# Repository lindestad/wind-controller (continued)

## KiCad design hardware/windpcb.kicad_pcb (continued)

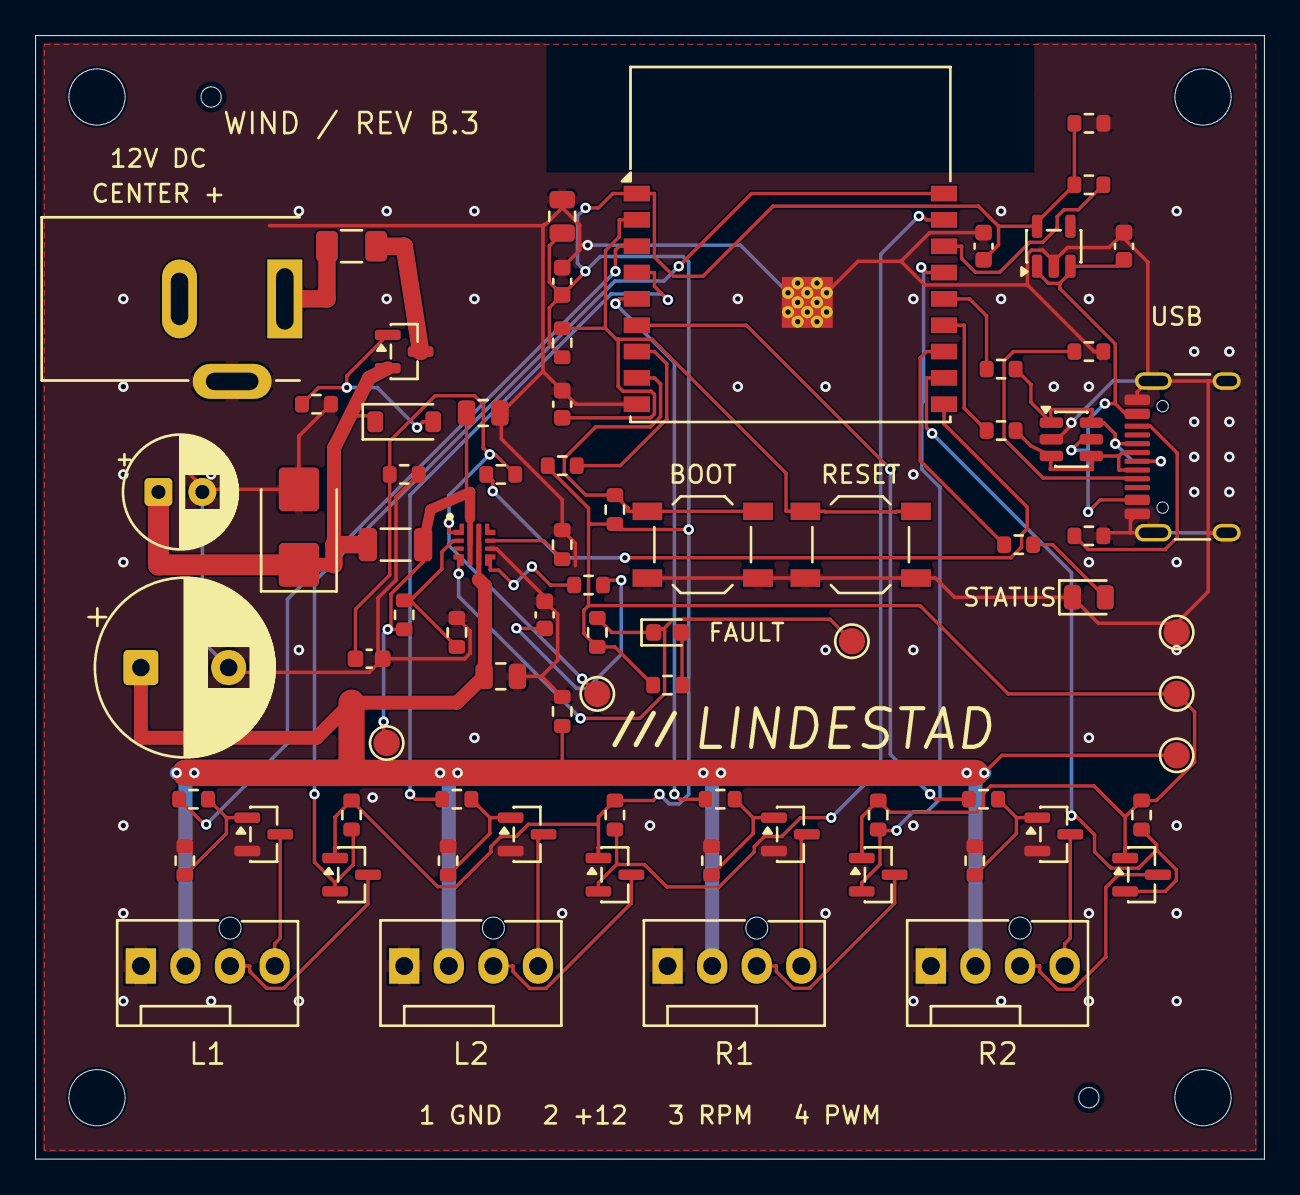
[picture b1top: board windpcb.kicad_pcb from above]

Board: 2 copper layers, 70.0 x 64.0 mm, 82 parts (0 on the bottom side), 49 nets.

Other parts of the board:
H1, H2, H3, H4: M3; MountingHole_3.2mm_M3
H5, H6: JLC TOOL 1.152 NPTH; JLC_Tooling_1.152

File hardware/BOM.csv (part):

Reference,Value,MPN,LCSC,Footprint,Assembly,Notes
U1,ESP32-C3-WROOM-02-N4,ESP32-C3-WROOM-02-N4,C2934560,Wind:RF_Module_ESP32-C3-WROOM-02,SMT,
J2,USB-C DATA,TYPE-C-31-M-12,C165948,Wind:Connector_USB_USB_C_Receptacle_HRO_TYPE-C-31-M-12,SMT,Retained HRO TYPE-C-31-M-12: stocked economical 16-pin USB2 receptacle; shell PTH joints are part of factory assembly.
R1,5.1k,0603WAF5101T5E,C23186,Wind:Resistor_SMD_R_0603_1608Metric,SMT,
R2,5.1k,0603WAF5101T5E,C23186,Wind:Resistor_SMD_R_0603_1608Metric,SMT,
U3,USBLC6-2SC6,USBLC6-2SC6,C7519,Wind:Package_TO_SOT_SMD_SOT-23-6,SMT,
R3,22,0603WAF220JT5E,C23345,Wind:Resistor_SMD_R_0603_1608Metric,SMT,"Basic; 22 ohm 0603 1%, 100 mW. Reject auto-matched ET7222 IC."
R4,22,0603WAF220JT5E,C23345,Wind:Resistor_SMD_R_0603_1608Metric,SMT,"Basic; 22 ohm 0603 1%, 100 mW. Reject auto-matched ET7222 IC."
U2,AP2112K-3.3,AP2112K-3.3TRG1,C51118,Wind:Package_TO_SOT_SMD_SOT-23-5,SMT,
C1,1uF / 50V,CL10A105KB8NNNC,C15849,Wind:Capacitor_SMD_C_0603_1608Metric,SMT,"Basic; 0603 X5R 10%; logic decoupling, -55 to +85 C dielectric range."
C2,1uF / 50V,CL10A105KB8NNNC,C15849,Wind:Capacitor_SMD_C_0603_1608Metric,SMT,"Basic; 0603 X5R 10%; logic decoupling, -55 to +85 C dielectric range."
C3,10uF / 50V,GRM21BR61H106KE43L,C440198,Wind:Capacitor_SMD_C_0805_2012Metric,SMT,Basic; 0805 X5R 10%; 3.3 V reservoir.
C4,100nF / 50V,CC0603KRX7R9BB104,C14663,Wind:Capacitor_SMD_C_0603_1608Metric,SMT,Basic; 0603 X7R 10%.
R5,10k,0603WAF1002T5E,C25804,Wind:Resistor_SMD_R_0603_1608Metric,SMT,
C5,1uF / 50V,CL10A105KB8NNNC,C15849,Wind:Capacitor_SMD_C_0603_1608Metric,SMT,"Basic; 0603 X5R 10%; logic decoupling, -55 to +85 C dielectric range."
R6,10k,0603WAF1002T5E,C25804,Wind:Resistor_SMD_R_0603_1608Metric,SMT,
R7,10k,0603WAF1002T5E,C25804,Wind:Resistor_SMD_R_0603_1608Metric,SMT,
R8,10k,0603WAF1002T5E,C25804,Wind:Resistor_SMD_R_0603_1608Metric,SMT,
SW1,BOOT,TL3342F160QG,C2886898,Wind:Button_Switch_SMD_SW_SPST_TL3342,SMT,Original E-Switch SMD switch is stocked; do not use through-hole TL1220 RESET auto-match.
SW2,RESET,TL3342F160QG,C2886898,Wind:Button_Switch_SMD_SW_SPST_TL3342,SMT,Original E-Switch SMD switch is stocked; do not use through-hole TL1220 RESET auto-match.
R9,1k,0603WAF1001T5E,C21190,Wind:Resistor_SMD_R_0603_1608Metric,SMT,
D3,STATUS GREEN,KT-0805G,C2297,Wind:LED_SMD_LED_0805_2012Metric,SMT,Basic green 0805; pad 1 cathode; brightness at low current requires first-board check
J1,12V / CENTER +,DC-005-5A-2.5,C381115,Wind:BarrelJack_XKB_DC-005-5A-2.5,THT,"XKB 5A; 5.5/2.5mm centre-positive plug, 9mm insertion. Pin 1 centre, pin 3 sleeve, pin 2 switched sleeve NC. Bottom-view drawing mirrored to top: pin2 axial -6mm, pin3 axial -3mm / transverse +4.7mm."
F1,3A / 32V,0466003.NRHF,C14165,Wind:Fuse_Fuse_1206_3216Metric,SMT,"Littelfuse 466 1206 fast 3A 32V; input backup fuse, not calibrated fan current limiter"
Q1,AO3401A,AO3401A,C15127,Wind:Package_TO_SOT_SMD_SOT-23,SMT,Reverse protection: drain faces input; source faces load
R10,4.7k,0603WAF4701T5E,C23162,Wind:Resistor_SMD_R_0603_1608Metric,SMT,Biases 9.1V reverse-FET gate clamp
D1,BZT52C9V1,BZT52C9V1-7-F,C260913,Wind:Diode_SMD_D_SOD-123,SMT,9.1V gate-source clamp; AO3401A absolute Vgs is 12V
D2,SMBJ15A TVS,SMBJ15A,C83846,Wind:Diode_SMD_D_SMB,SMT,"Littelfuse; unidirectional SMB/DO-214AA, 15 V standoff, 24.4 V rated clamp; stocked exact electrical type."
C6,47uF / 50V,EEUFR1H470,C407950,Wind:Capacitor_THT_CP_Radial_D6.3mm_P2.50mm,THT,"Panasonic FR: 6.3mm diameter, 11.2mm body, 2.5mm lead spacing"
FB1,120R@100MHz / 3.5A,BLM31PG121SN1L,C85841,Wind:Inductor_SMD_L_1206_3216Metric,SMT,
C7,1uF / 50V,CL21B105KBFNNNE,C28323,Wind:Capacitor_SMD_C_0805_2012Metric,SMT,Basic; 0805 X7R 50 V 10%.
U4,TPS25970LRPWR,TPS25970LRPWR,C3662801,Wind:TPS25970_RPW0010A_2x2mm,SMT,
R11,97.6k 0.1%,RT0603BRE0797K6L,C862326,Wind:Resistor_SMD_R_0603_1608Metric,SMT,"Stock replacement for C861608 shortfall; 97.6k 0.1%, 50 ppm/C (previously 25 ppm/C). See drift calculation."
R12,10k 0.1%,RT0603BRD0710KL,C95204,Wind:Resistor_SMD_R_0603_1608Metric,SMT,"Retain 10k 0.1%, 25 ppm/C for OVLO divider."
R13,2.4k 1%,0603WAF2401T5E,C22940,Wind:Resistor_SMD_R_0603_1608Metric,SMT,"Basic ILIM resistor: nominal 2.395 A; 1%, 100 ppm/C"
C8,100nF / 50V,CC0603KRX7R9BB104,C14663,Wind:Capacitor_SMD_C_0603_1608Metric,SMT,100 nF X7R; ~0.36 s nominal 12 V slew; firmware waits 750 ms with PWM stopped
R14,1k,0603WAF1001T5E,C21190,Wind:Resistor_SMD_R_0603_1608Metric,SMT,
R15,10k,0603WAF1002T5E,C25804,Wind:Resistor_SMD_R_0603_1608Metric,SMT,
C11,100nF / 50V,CC0603KRX7R9BB104,C14663,Wind:Capacitor_SMD_C_0603_1608Metric,SMT,Basic; 0603 X7R 10%.
C9,470uF / 25V,EEUFR1E471,C407944,Wind:Capacitor_THT_CP_Radial_D10.0mm_P5.00mm,THT,"Panasonic FR 470uF 25V: D10 x H12.5mm, pitch 5mm; impedance 43mohm, ripple 1.29A at 100kHz; same capacitance and voltage."
C10,1uF / 50V,CL21B105KBFNNNE,C28323,Wind:Capacitor_SMD_C_0805_2012Metric,SMT,Basic; 0805 X7R 50 V 10%.
R16,4.7k,0603WAF4701T5E,C23162,Wind:Resistor_SMD_R_0603_1608Metric,SMT,"Output discharge: ~2.2 s RC with 470uF, not an instantaneous discharge"
R17,10k,0603WAF1002T5E,C25804,Wind:Resistor_SMD_R_0603_1608Metric,SMT,
D4,FAULT RED,KT-0603R,C2286,Wind:LED_SMD_LED_0603_1608Metric,SMT,KENTO Basic red 0603; replaces Extended LED to avoid one feeder fee. Preserve pad 1 cathode.
R18,2.2k,0603WAF2201T5E,C4190,Wind:Resistor_SMD_R_0603_1608Metric,SMT,
J3,L1,470531000,C240840,Wind:Connector_FanPinHeader_1x04_P2.54mm_Vertical,THT,"Genuine Molex 47053-1000, natural white, factory wave soldering; exact existing keyed fan footprint."
Q2,SI2312-TP,SI2312-TP,C6488168,Wind:Package_TO_SOT_SMD_SOT-23,SMT,MCC exact part; G1/S2/D3; RDS(on) specified at VGS=1.8 V
R20,100,0603WAF1000T5E,C22775,Wind:Resistor_SMD_R_0603_1608Metric,SMT,"Basic; 100 ohm 0603 1%, 100 mW."
R21,100k,0603WAF1003T5E,C25803,Wind:Resistor_SMD_R_0603_1608Metric,SMT,
R22,2.2k,0603WAF2201T5E,C4190,Wind:Resistor_SMD_R_0603_1608Metric,SMT,MCU-side tach pull-up; Q6-Q9 separate raw fan voltage
J4,L2,470531000,C240840,Wind:Connector_FanPinHeader_1x04_P2.54mm_Vertical,THT,"Genuine Molex 47053-1000, natural white, factory wave soldering; exact existing keyed fan footprint."
Q3,SI2312-TP,SI2312-TP,C6488168,Wind:Package_TO_SOT_SMD_SOT-23,SMT,MCC exact part; G1/S2/D3; RDS(on) specified at VGS=1.8 V
R25,100,0603WAF1000T5E,C22775,Wind:Resistor_SMD_R_0603_1608Metric,SMT,"Basic; 100 ohm 0603 1%, 100 mW."
R26,100k,0603WAF1003T5E,C25803,Wind:Resistor_SMD_R_0603_1608Metric,SMT,
R27,2.2k,0603WAF2201T5E,C4190,Wind:Resistor_SMD_R_0603_1608Metric,SMT,MCU-side tach pull-up; Q6-Q9 separate raw fan voltage
J5,R1,470531000,C240840,Wind:Connector_FanPinHeader_1x04_P2.54mm_Vertical,THT,"Genuine Molex 47053-1000, natural white, factory wave soldering; exact existing keyed fan footprint."
Q4,SI2312-TP,SI2312-TP,C6488168,Wind:Package_TO_SOT_SMD_SOT-23,SMT,MCC exact part; G1/S2/D3; RDS(on) specified at VGS=1.8 V
R30,100,0603WAF1000T5E,C22775,Wind:Resistor_SMD_R_0603_1608Metric,SMT,"Basic; 100 ohm 0603 1%, 100 mW."
R31,100k,0603WAF1003T5E,C25803,Wind:Resistor_SMD_R_0603_1608Metric,SMT,
R32,2.2k,0603WAF2201T5E,C4190,Wind:Resistor_SMD_R_0603_1608Metric,SMT,MCU-side tach pull-up; Q6-Q9 separate raw fan voltage
J6,R2,470531000,C240840,Wind:Connector_FanPinHeader_1x04_P2.54mm_Vertical,THT,"Genuine Molex 47053-1000, natural white, factory wave soldering; exact existing keyed fan footprint."
Q5,SI2312-TP,SI2312-TP,C6488168,Wind:Package_TO_SOT_SMD_SOT-23,SMT,MCC exact part; G1/S2/D3; RDS(on) specified at VGS=1.8 V
R35,100,0603WAF1000T5E,C22775,Wind:Resistor_SMD_R_0603_1608Metric,SMT,"Basic; 100 ohm 0603 1%, 100 mW."
R36,100k,0603WAF1003T5E,C25803,Wind:Resistor_SMD_R_0603_1608Metric,SMT,
R37,2.2k,0603WAF2201T5E,C4190,Wind:Resistor_SMD_R_0603_1608Metric,SMT,MCU-side tach pull-up; Q6-Q9 separate raw fan voltage
TP1,GND,PCB test point,,Wind:TestPoint_TestPoint_Pad_D1.5mm,PCB,
TP2,+3V3,PCB test point,,Wind:TestPoint_TestPoint_Pad_D1.5mm,PCB,
TP3,FAN_12V,PCB test point,,Wind:TestPoint_TestPoint_Pad_D1.5mm,PCB,
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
